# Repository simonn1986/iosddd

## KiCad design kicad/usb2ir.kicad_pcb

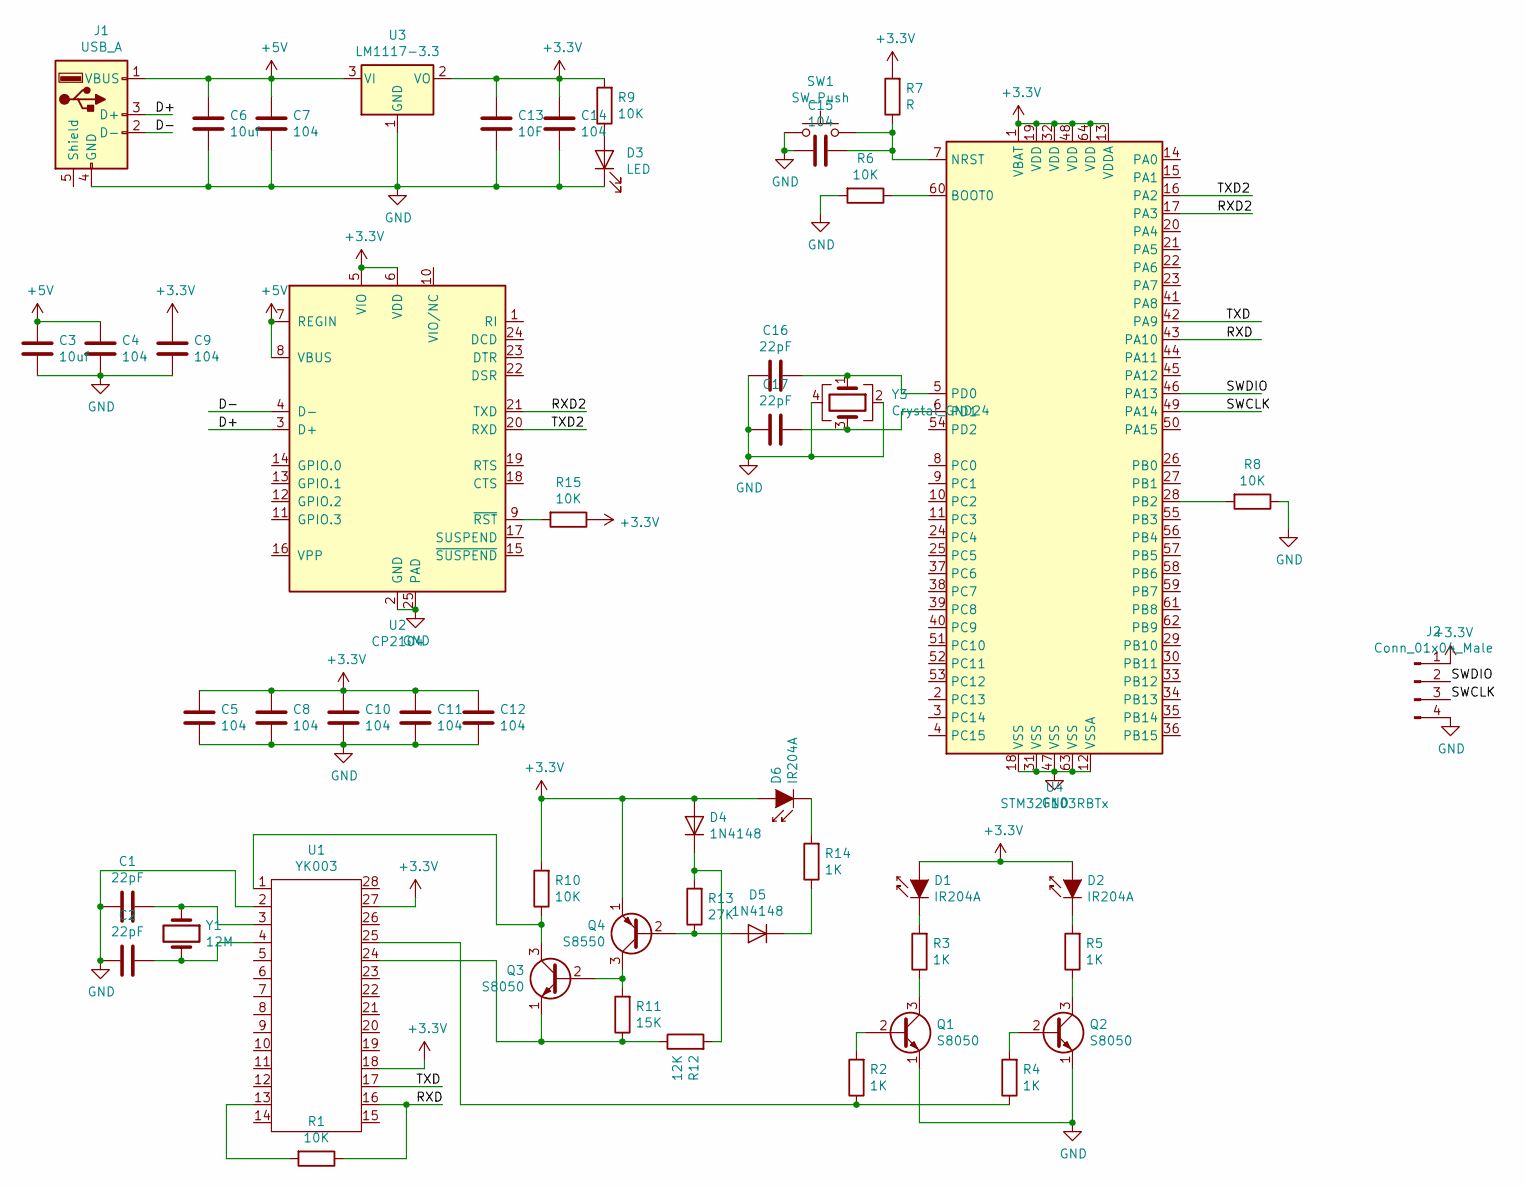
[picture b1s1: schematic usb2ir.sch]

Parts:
C1, C2, C16, C17: 22pF; C_0603_1608Metric
C3, C6: 10uf; C_0603_1608Metric
C4, C5, C7, C8, C9, C10, C11, C12, C14, C15: 104; C_0603_1608Metric
C13: 10F; C_0603_1608Metric
D1, D2, D6: IR204A; LED_D3.0mm_IRBlack
D3: LED; LED_0603_1608Metric_Castellated
D4, D5: 1N4148; D_0603_1608Metric_Castellated
J1: USB_A; USB_A_CNCTech_1001-011-01101_Horizontal
J2: Conn_01x04_Male; PinHeader_1x04_P2.54mm_Vertical
Q1, Q2, Q3: S8050; SOT-23
Q4: S8550; SOT-23
R1, R6, R8, R9, R10, R15: 10K; R_0603_1608Metric_Pad1.05x0.95mm_HandSolder
R2, R3, R4, R5, R14: 1K; R_0603_1608Metric_Pad1.05x0.95mm_HandSolder
R7: R; R_0603_1608Metric_Pad1.05x0.95mm_HandSolder
R11: 15K; R_0603_1608Metric_Pad1.05x0.95mm_HandSolder
R12: 12K; R_0603_1608Metric_Pad1.05x0.95mm_HandSolder
R13: 27K; R_0603_1608Metric_Pad1.05x0.95mm_HandSolder
SW1: SW_Push; SW_SPST_FSMSM
U1: YK003; TSSOP-28_4.4x9.7mm_P0.65mm
U2: CP2104; QFN-24-1EP_4x4mm_P0.5mm_EP2.6x2.6mm
U3: LM1117-3.3; SOT-223
U4: STM32F103RBTx; LQFP-64_10x10mm_P0.5mm
Y1: 12M; Crystal_SMD_5032-2Pin_5.0x3.2mm
Y3: Crystal_GND24; Crystal_SMD_5032-4Pin_5.0x3.2mm

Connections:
+3V3: C5.1, C8.1, C9.1, C10.1, C11.1, C12.1, C13.1, C14.1, D1.2 (A), D2.2 (A), D4.2 (A), D6.2 (A), J2.1, Q4.1 (E), R7.2, R9.2, R10.2, R15.1, U1.18, U1.27, U2.5 (VIO), U2.6 (VDD), U3.2 (VO), U4.1 (VBAT), U4.13 (VDDA), U4.19 (VDD), U4.32 (VDD), U4.48 (VDD), U4.64 (VDD)
+5V: C3.1, C4.1, C6.1, C7.1, J1.1 (VBUS), U2.7 (REGIN), U2.8 (VBUS), U3.3 (VI)
/D+: J1.3 (D+), U2.3 (D+)
/D-: J1.2 (D-), U2.4 (D-)
/RXD: R1.1, U1.16, U4.43 (PA10)
/RXD2: U2.21 (TXD), U4.17 (PA3)
/SWCLK: J2.3, U4.49 (PA14)
/SWDIO: J2.2, U4.46 (PA13)
/TXD: U1.17, U4.42 (PA9)
/TXD2: U2.20 (RXD), U4.16 (PA2)
GND: C1.2, C2.2, C3.2, C4.2, C5.2, C6.2, C7.2, C8.2, C9.2, C10.2, C11.2, C12.2, C13.2, C14.2, C15.2, C16.2, C17.2, D3.1 (K), J1.4 (GND), J2.4, Q1.1 (E), Q2.1 (E), R6.2, R8.1, SW1.1, U1.2, U2.2 (GND), U2.25 (PAD), U3.1 (GND), U4.12 (VSSA), U4.18 (VSS), U4.31 (VSS), U4.47 (VSS), U4.63 (VSS), Y3.2, Y3.4
unnamed: C1.1, U1.3, Y1.1
unnamed: C2.1, U1.4, Y1.2
unnamed: C15.1, R7.1, SW1.2, U4.7 (NRST)
unnamed: C16.1, U4.5 (PD0), Y3.1
unnamed: C17.1, U4.6 (PD1), Y3.3
unnamed: D1.1 (K), R3.2
unnamed: D2.1 (K), R5.2
unnamed: D3.2 (A), R9.1
unnamed: D4.1 (K), R12.2, R13.2
unnamed: D5.1 (K), R14.1
unnamed: D5.2 (A), Q4.2 (B), R13.1
unnamed: D6.1 (K), R14.2
unnamed: Q1.2 (B), R2.2
unnamed: Q1.3 (C), R3.1
unnamed: Q2.2 (B), R4.2
unnamed: Q2.3 (C), R5.1
unnamed: Q3.1 (E), R11.1, R12.1, U1.24
unnamed: Q3.2 (B), Q4.3 (C), R11.2
unnamed: Q3.3 (C), R10.1, U1.1
unnamed: R1.2, U1.13
unnamed: R2.1, R4.1, U1.25
unnamed: R6.1, U4.60 (BOOT0)
unnamed: R8.2, U4.28 (PB2)
unnamed: R15.2, U2.9 (~RST)

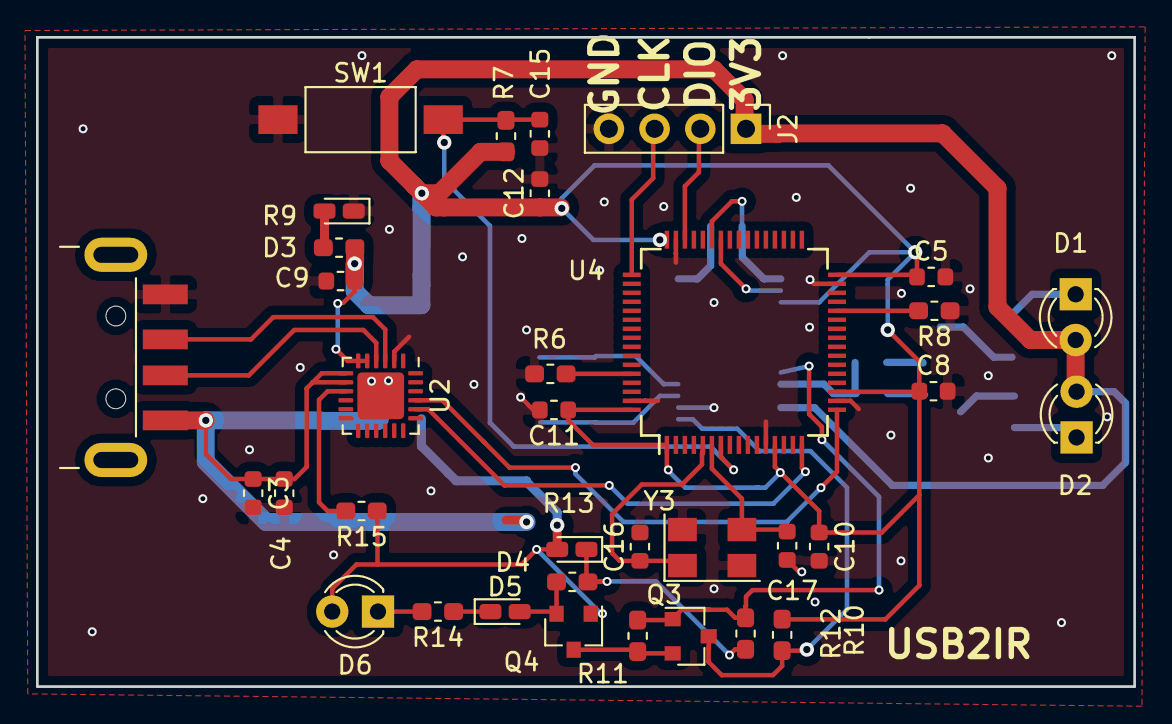
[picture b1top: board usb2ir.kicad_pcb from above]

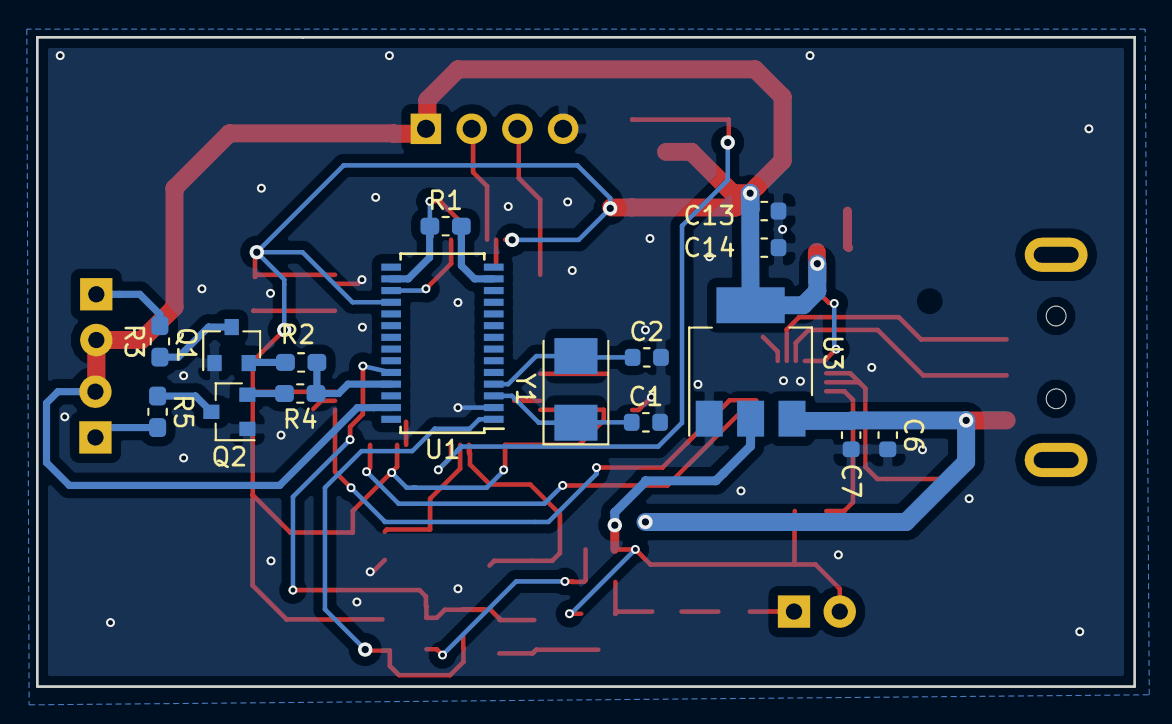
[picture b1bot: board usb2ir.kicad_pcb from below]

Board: 2 copper layers, 61.0 x 36.1 mm, 51 parts (16 on the bottom side), 35 nets.

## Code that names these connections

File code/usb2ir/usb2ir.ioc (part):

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Mcu.Name=STM32F103R(8-B)Tx
Mcu.Package=LQFP64
Mcu.UserName=STM32F103RBTx
PA10.Mode=Asynchronous
PA10.Signal=USART1_RX
PA2.Mode=Asynchronous
PA2.Signal=USART2_TX
PA3.Mode=Asynchronous
PA3.Signal=USART2_RX
PA9.Mode=Asynchronous
PA9.Signal=USART1_TX
PD0-OSC_IN.Mode=HSE-External-Oscillator
PD0-OSC_IN.Signal=RCC_OSC_IN
PD1-OSC_OUT.Mode=HSE-External-Oscillator
PD1-OSC_OUT.Signal=RCC_OSC_OUT
board=custom

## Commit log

2019-06-20 个人使用的home assistant红外设备，开源kicad画电路图
2019-06-20 STM32CubeMX生成MDK串口工程
2019-06-21 添加串口控制红外程序
2019-07-16 硬件添加红外复制功能
2019-07-19 程序上添加红外复制功能
2019-09-14 程序上额外增加一个红外复制函数，方便调用
2023-09-18 经过长时间的运行发现CH340G偶尔会出现数据丢失情况故现改用cp2104增加稳定性
